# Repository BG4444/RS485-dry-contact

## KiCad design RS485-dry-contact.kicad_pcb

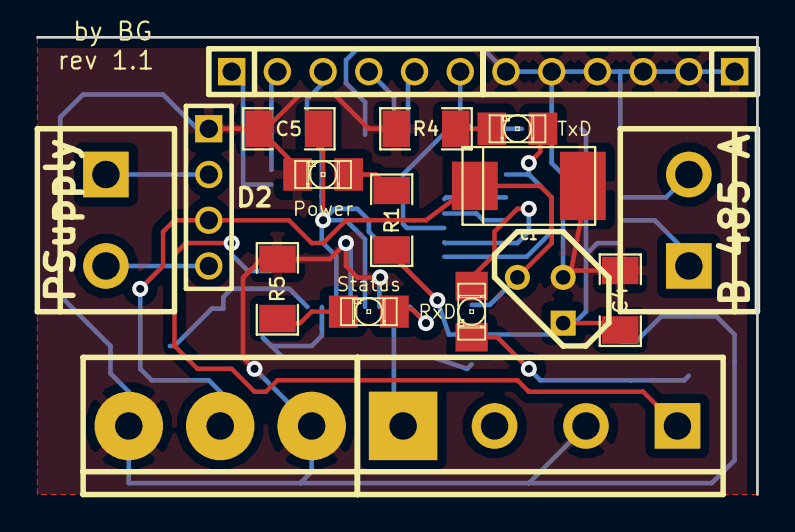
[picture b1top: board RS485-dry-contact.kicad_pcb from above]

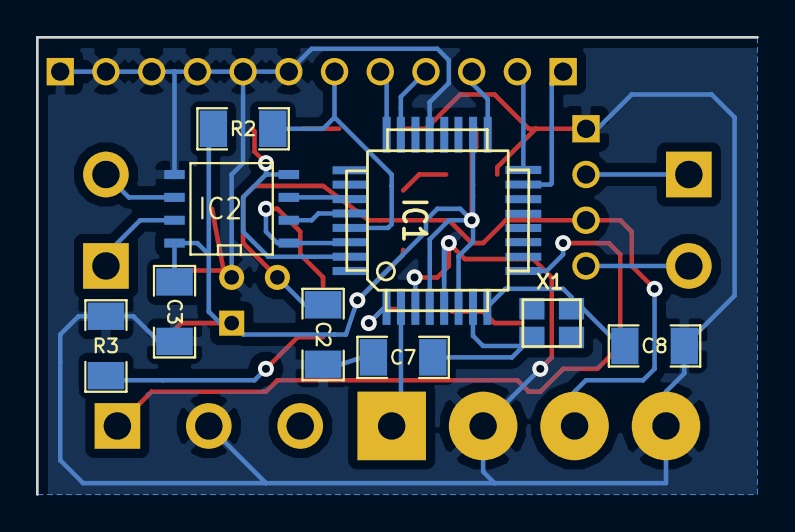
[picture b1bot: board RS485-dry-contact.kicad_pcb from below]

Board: 2 copper layers, 40.0 x 25.4 mm, 16 parts (9 on the bottom side), 10 nets.

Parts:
C1: c_tant_D
C2, C3, C4, C5, C7, C8: SM1206
D2: PIN_ARRAY_4x1
IC1: TQFP32
IC2: SO8N
R1, R2, R3, R4, R5: SM1206
X1: crystal_FA238-TSX3225

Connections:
GND: C1.2, C2.1, C3.1, C4.2, C5.2, C7.1, C8.1, D2.1, IC1.3, IC1.5, IC1.21, IC2.5, R3.2, R4.2, R5.2
unnamed: IC1.29, R2.1
unnamed: IC1.30, IC2.1
unnamed: IC1.31, IC2.4
unnamed: IC1.28, IC2.2
unnamed: IC1.27, IC2.3
unnamed: C1.1, C2.2, D2.3
unnamed: C8.2, IC1.8, X1.2
unnamed: C7.2, IC1.7, X1.1
VCC: C3.2, C4.1, C5.1, IC1.4, IC1.6, IC1.18, IC2.8, R1.2, R2.2

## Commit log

2015-04-11 Sceme draft
2015-04-11 remove arv-isp
2015-04-11 draft
2015-04-12 Rev 1.0
2015-04-13 Rev 1.1
2015-04-14 Add Gerbers
2015-04-14 Add Masks
2015-04-20 Добавлен список компонентов
2015-04-26 Writing tests
2015-04-26 Pushed first test - status blink
2015-04-26 Add test 2 - solo
2015-04-26 Firmware rev 0.9
2015-04-29 Added test 03-bytefall
2015-05-03 First try to detect collision
2015-05-06 add eep-files 0x0 0x3 0x7
2015-05-16 collision test beta
2015-05-17 bugfix
2015-05-17 bugfix2
2015-05-17 bugfix3
